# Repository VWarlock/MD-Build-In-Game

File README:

Build-In Game Project for Sega Genesis / Mega Drive  
===================================================  
  
Main idea by ArcadeTV  
Development by srdwa, ArcadeTV and borti4938  
  
See logs and discussions here: http://circuit-board.de/forum/index.php/Thread/17706-Idee-Mega-Drive-mit-eingebautem-Spiel/  
  
===================================================  

This work here is still WIP!!! It has been never tested so far!!!  

===================================================  

Main idea:  
- start a game from internal rom if no device is present at the extension port or no cartridge is present  
- use indentification signals from cart slot and extension slot for detection  
- internal rom can be separated in one, two or four banks (selected by two pins)  
- bank switch is accessed by a 2bit counter  
- TMSS disable mod as described here: http://assemblergames.com/l/threads/md-genny-auto-switching-tmss-bypass-mod.19781/ can be enabled optionally  
  
===================================================  
  
ToDo:  
- update PCB version  
- test 2bit counter addition for switchless code (code by borti4938)  
- write installation tips  
  
===================================================  
  
Pinout of the PLD (G16V8) as used on the PCB:  
  
/* *************** INPUT PINS ******************** */  
PIN  1 = DISKn;     /* /DISK (ExpPort B2)                       */  
PIN  2 = ROM_Mode2; /* high/open = 1 game     , low = 2 games   */  
PIN  3 = ROM_Mode4; /* high/open = 1/2 game(s), low = 4 games   */  
                    /* low = 4 games (beats ROM_Mode2)          */  
PIN  4 = CARTn;     /* /CART (from ASIC cart slot B32,          */  
                    /*        cutted from ASIC)                 */  
PIN  5 = ASIC_OEn;  /* /OE (from ASIC; cutted from cart slot    */  
                    /*                 B17 if TMSS Mod is used) */  
PIN  6 = CEn;       /* /CE (cart slot B16)                      */  
PIN  7 = A23;       /* A23 (cart slot B11)                      */  
PIN  8 = AMSB0;     /* A19 (cart slot  B7)                      */  
PIN  9 = AMSB1;     /* A20 (cart slot  B8)                      */  
                    /* (addressbus counts from A1)              */  
  
/* *************** I/O PINS ******************** */  
PIN 19 = BIG_Sel0;   /* bank switch LSB                         */  
PIN 18 = BIG_Sel1;   /* bank switch MSB                         */  
PIN 17 = ASIC_CARTn; /* /CART (from ASIC; cutted from cart      */  
                     /*                   slot B32)             */  
PIN 16 = ROM_OEn;    /* /OE internal EEPROM (29F1610 Pin 14)    */  
PIN 15 = ROM_CEn;    /* /CE internal EEPROM (29F1610 Pin 12)    */  
PIN 14 = CART_OEn;   /* /OE cartridge (cart slot B17)           */  
PIN 13 = ROM_AMSB0;  /* A18 internal EEPROM (29F1610 Pin  2)    */  
PIN 12 = ROM_AMSB1;  /* A19 internal EEPROM (29F1610 Pin 43)    */  
PIN 11 = TMSS_ENn;   /* high = disabled, low = enabled          */  
                     /* /M3 (cart slot B30) AND TMSS-Mod_en     */

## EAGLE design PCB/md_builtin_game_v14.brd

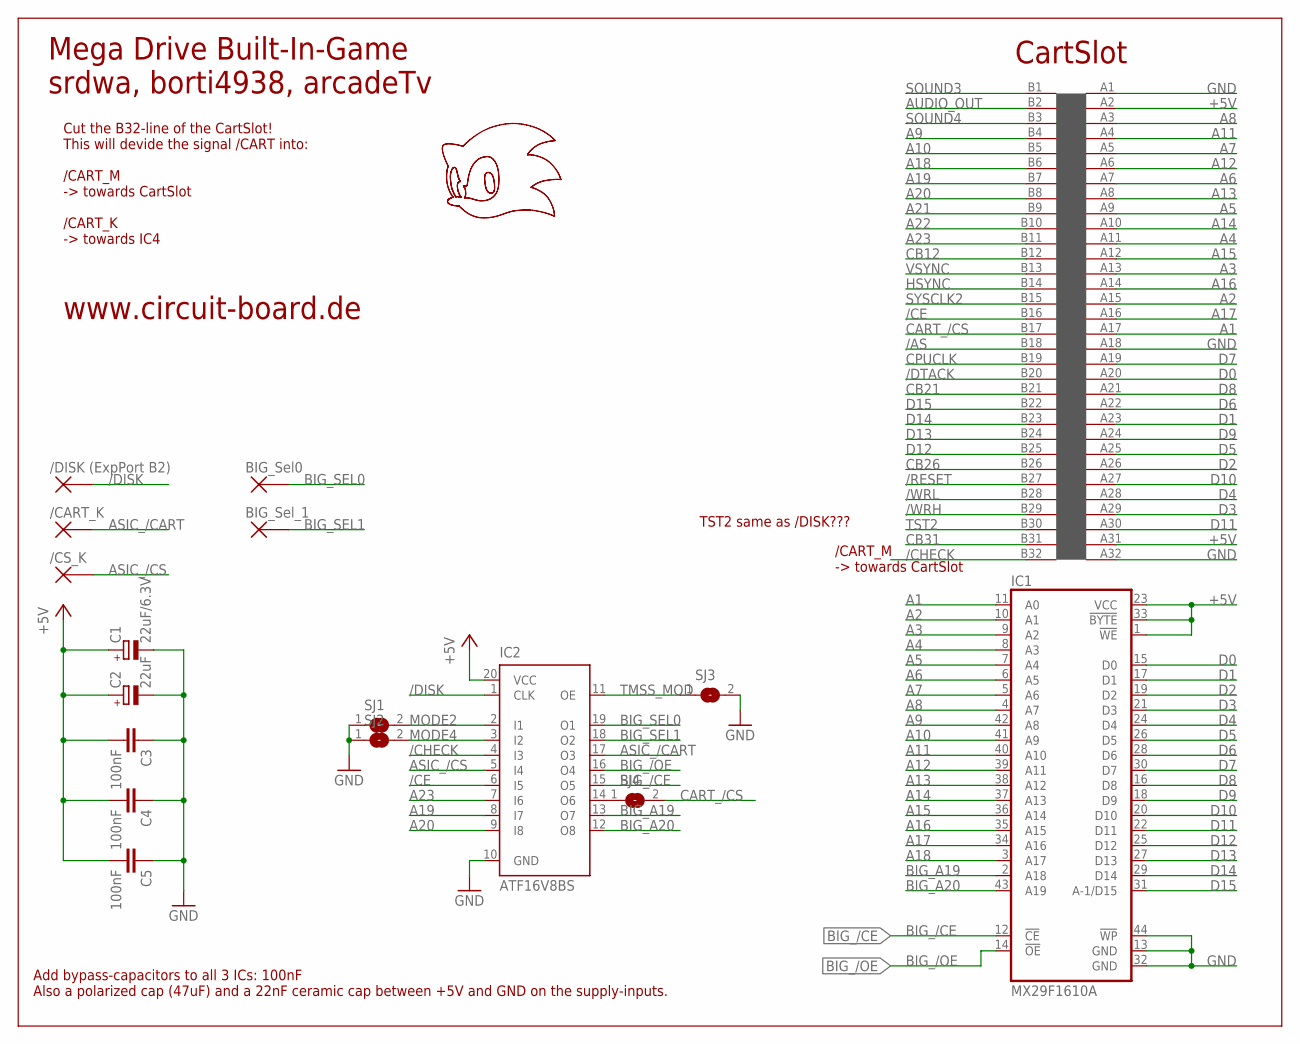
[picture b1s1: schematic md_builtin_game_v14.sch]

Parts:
C1: 22uF/6.3V; SMC_B
C2: 22uF; SMC_B
C3, C4, C5: 100nF; Z0805
IC1: MX29F1610A; SO44
IC2: ATF16V8BS; SO20L
SJ1, SJ2, SJ3, SJ4: SJ
U$1: LOGO_SONIC_20MM
U$2: /CS_K; PADS
U$3: /CART_K; PADS
U$4: /DISK (ExpPort B2); PADS
U$5: BIG_Sel0; PADS
U$6: MEGADRIVE_EDGE_CONNECTOR
U$7: BIG_Sel_1; PADS

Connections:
+5V: C1.+, C2.+, C3.2, C4.2, C5.2, IC1.1 (!WE), IC1.23 (VCC), IC1.33 (!BYTE), IC2.20 (VCC), U$6.A2, U$6.A31
/AS: U$6.B18
/CE: IC2.6 (I5), U$6.B16
/CHECK: IC2.4 (I3), U$6.B32
/DISK: IC2.1 (CLK), U$4.P$1
/DTACK: U$6.B20
/RESET: U$6.B27
/WRH: U$6.B29
/WRL: U$6.B28
A1: IC1.11 (A0), U$6.A17
A2: IC1.10 (A1), U$6.A15
A3: IC1.9 (A2), U$6.A13
A4: IC1.8 (A3), U$6.A11
A5: IC1.7 (A4), U$6.A9
A6: IC1.6 (A5), U$6.A7
A7: IC1.5 (A6), U$6.A5
A8: IC1.4 (A7), U$6.A3
A9: IC1.42 (A8), U$6.B4
A10: IC1.41 (A9), U$6.B5
A11: IC1.40 (A10), U$6.A4
A12: IC1.39 (A11), U$6.A6
A13: IC1.38 (A12), U$6.A8
A14: IC1.37 (A13), U$6.A10
A15: IC1.36 (A14), U$6.A12
A16: IC1.35 (A15), U$6.A14
A17: IC1.34 (A16), U$6.A16
A18: IC1.3 (A17), U$6.B6
A19: IC2.8 (I7), U$6.B7
A20: IC2.9 (I8), U$6.B8
A21: U$6.B9
A22: U$6.B10
A23: IC2.7 (I6), U$6.B11
ASIC_/CART: IC2.17 (O3), U$3.P$1
ASIC_/CS: IC2.5 (I4), U$2.P$1
AUDIO_OUT: U$6.B2
BIG_/CE: IC1.12 (!CE), IC2.15 (O5)
BIG_/OE: IC1.14 (!OE), IC2.16 (O4)
BIG_A19: IC1.2 (A18), IC2.13 (O7)
BIG_A20: IC1.43 (A19), IC2.12 (O8)
BIG_SEL0: IC2.19 (O1), U$5.P$1
BIG_SEL1: IC2.18 (O2), U$7.P$1
CART_/CS: SJ4.2, U$6.B17
CB12: U$6.B12
CB21: U$6.B21
CB26: U$6.B26
CB31: U$6.B31
CPUCLK: U$6.B19
D0: IC1.15 (D0), U$6.A20
D1: IC1.17 (D1), U$6.A23
D2: IC1.19 (D2), U$6.A26
D3: IC1.21 (D3), U$6.A29
D4: IC1.24 (D4), U$6.A28
D5: IC1.26 (D5), U$6.A25
D6: IC1.28 (D6), U$6.A22
D7: IC1.30 (D7), U$6.A19
D8: IC1.16 (D8), U$6.A21
D9: IC1.18 (D9), U$6.A24
D10: IC1.20 (D10), U$6.A27
D11: IC1.22 (D11), U$6.A30
D12: IC1.25 (D12), U$6.B25
D13: IC1.27 (D13), U$6.B24
D14: IC1.29 (D14), U$6.B23
D15: IC1.31 (A-1/D15), U$6.B22
GND: C1.-, C2.-, C3.1, C4.1, C5.1, IC1.13 (GND), IC1.32 (GND), IC1.44 (!WP), IC2.10 (GND), SJ1.1, SJ2.1, SJ3.2, U$6.A1, U$6.A18, U$6.A32
HSYNC: U$6.B14
MODE2: IC2.2 (I1), SJ1.2
MODE4: IC2.3 (I2), SJ2.2
unnamed: IC2.14 (O6), SJ4.1
SOUND3: U$6.B1
SOUND4: U$6.B3
SYSCLK2: U$6.B15
TMSS_MOD: IC2.11 (OE), SJ3.1
TST2: U$6.B30
VSYNC: U$6.B13

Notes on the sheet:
Cut the B32-line of the CartSlot! This will devide the signal /CART into: /CART_M -> towards CartSlot /CART_K -> towards IC4
Mega Drive Built-In-Game srdwa, borti4938, arcadeTv
Add bypass-capacitors to all 3 ICs: 100nF Also a polarized cap (47uF) and a 22nF ceramic cap between +5V and GND on the supply-inputs.
CartSlot
www.circuit-board.de
/CART_M -> towards CartSlot
TST2 same as /DISK???

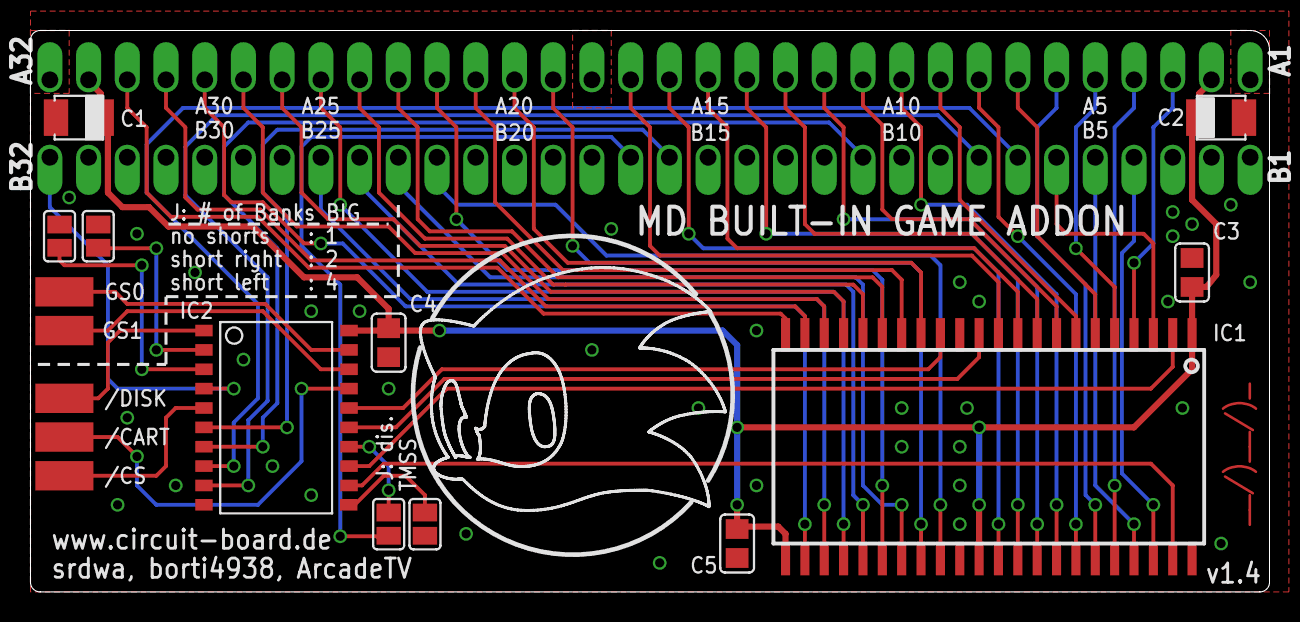
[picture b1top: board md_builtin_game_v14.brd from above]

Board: 2 copper layers, 81.3 x 36.8 mm, 18 parts (0 on the bottom side), 55 nets.

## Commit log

2015-10-20 Documentation update - there was a small mistake in the pinout of the PLD
2015-10-21 revert small logic error for the TMSS disabler for the internal game
2015-10-23 code debugging, reset counter now works fine :)
2015-10-27 Change pinout, add alternative color scheme for LED - change pinout of video mode and language flags to come close to Seb’s solution (https://knzl.de/saturnmod/) avoiding confusions with MegaCD Multi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
2015-10-28 back changing pinout from commit 6da29fae63ec1528629ddc0af09562feddd8a9f9, minor code improvements - regarding the pinout: I was confused as the logic table given here (http://www.mmmonkey.co.uk/mcd/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
2016-01-25 PLD-Code Update to V2.0 - fix TMSS bypass mod - fix game selection (error in signal naming)
2016-01-25 Backup compatibility of code v2.0 (and above) to PCB v1.4
2016-01-25 change pinout, minor improvements - move reset button and out from pin 2 and 3 to 13 and 12 - simplify code after applying new mode - compatibility with MegaCD MultiBIOS
2016-01-25 use same status register for video mode, language mode and game selection counter
2016-01-26 remove not-needed macros
2016-01-26 bugfix: set initial mode was wrong
2016-01-26 bugfix: reset the mode counter was a reset for the game selection counter
2016-01-26 bugfix
2016-01-26 flash LED for a short moment if a push on the reset button is detected
2016-01-27 update switchless code - game selection counter pins are set up on each power cycle and doesn’t change with a reset - increasing the 2bit counter now on holding the reset button (the LED first cycles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
2016-01-27 Update PCB Version from v1.4 to v2.x - v2.1 has an optional (switchable) TMSS bypass mod included (TMSS bypass is enabled if /M30 (cart slot B30) is high and if the jumpers are set to on or to switch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
2016-01-27 Change /RoMC to negative logic RoMC (Reset on Mode Change) is described as negative logic. In the code the logic was positive.
2016-02-01 switch led completely off if a reset push is detected until reset button has been released (for a reset) or the PIC goes into the change mode loop This change is suitable for the IGR Add-on (https://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
